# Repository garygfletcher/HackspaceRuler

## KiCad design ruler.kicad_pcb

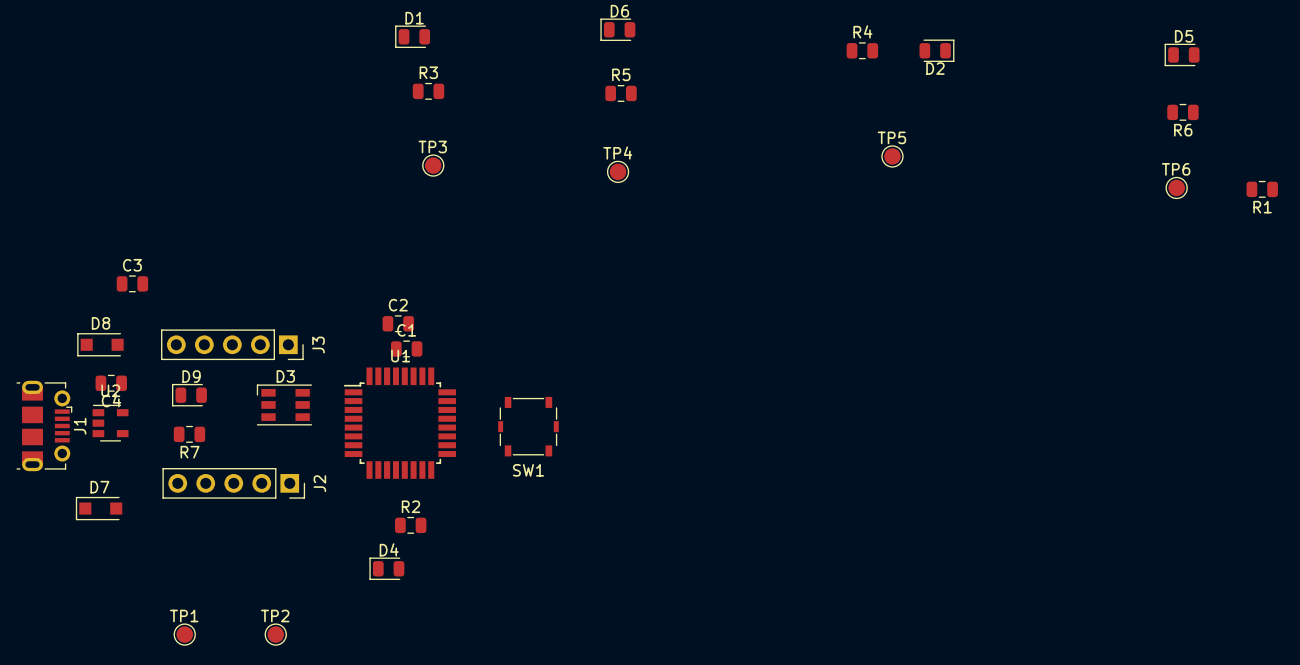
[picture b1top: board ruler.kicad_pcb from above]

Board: 2 copper layers, 32 parts (0 on the bottom side), 33 nets, no tracks yet.

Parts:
C1, C3: C; C_0805_2012Metric
C2: 1UF; C_0805_2012Metric
C4: 10UF; C_0805_2012Metric
D1, D6: LED-RED; LED_0805_2012Metric
D2, D9: LED-GREEN; LED_0805_2012Metric
D3: APA102; LED_RGB_PLCC-6
D4: LED-YELLOW; LED_0805_2012Metric
D5: LED-BLUE; LED_0805_2012Metric
D7, D8: D_Schottky; D_SOD-123F
J1: USB_B_Micro; USB_Micro-B_Molex-105017-0001
J2, J3: Conn_01x05_Female; PinSocket_1x05_P2.54mm_Vertical
R1: 2M; R_0805_2012Metric
R2, R3, R4, R5, R6: 2.2k; R_0805_2012Metric
R7: 10K; R_0805_2012Metric
SW1: SW_Push_Dual; SW_SPST_Panasonic_EVQPL_3PL_5PL_PT_A08
TP1, TP2, TP3, TP4, TP5, TP6: TestPoint; TestPoint_Pad_D1.5mm
U1: SAMD21E17A; TQFP-32_7x7mm_P0.8mm
U2: AP2112K-3.3; SOT-23-5

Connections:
+3V3: C2.1, C4.1, D3.4, J3.1, R7.2, U1.9, U1.30, U2.5
/CAP0: R1.2, TP6.1, U1.14
/CAP1: TP3.1, U1.6
/CAP2: TP4.1, U1.5
/CAP3: TP5.1, U1.4
/D0_A4_PA08_SDA: J3.4, U1.11
/D1_A0_PA02: J3.3, U1.3
/D2_A1_PA09_SCL_MISO: J3.2, U1.12
/D3_A3_PA07_RXD_SCK: J2.2, U1.8
/D4_A2_PA06_TXD_MOSI: J2.3, U1.7
/D+: J1.3, U1.24
/D-: J1.2, U1.23
/DOTSTAR_CLOCK: D3.2, U1.2
/DOTSTAR_DATA: D3.1, U1.1
/LED4: R3.2, U1.16
/LED5: R2.2, U1.15
/LED6: R4.2, U1.27
/LED7: R6.2, U1.25
/SWC: TP1.1, U1.31
/SWD: TP2.1, U1.32
/VBAT: D7.2, J2.5
/VBUS: D8.2, J1.1, J3.5
/nRESET: J2.1, SW1.2, U1.26
GND: C1.2, C2.2, C3.2, C4.2, D1.1, D2.1, D3.3, D4.1, D5.1, D6.1, D9.1, J1.5, J1.6, J2.4, R1.1, SW1.1, U1.10, U1.28, U2.2
unnamed: C1.1, U1.29
unnamed: C3.1, D7.1, D8.1, U2.1, U2.3
unnamed: D1.2, R3.1
unnamed: D2.2, R4.1
unnamed: D4.2, R2.1
unnamed: D5.2, R6.1
unnamed: D6.2, R5.1
unnamed: D9.2, R7.1
unnamed: R5.2, U1.13

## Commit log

2019-11-25 Schematic Complete
2019-11-25 laid things out
2019-12-02 updated schematic
2019-12-02 corrected folder structure
2019-12-02 updated legacy library path
